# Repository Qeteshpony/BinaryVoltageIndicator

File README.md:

# Binary Voltage Indicator

[Hardware Documentation](https://qeteshpony.github.io/BinaryVoltageIndicator)

A small board that can be attached to a 5V power supply to show if the voltage is above or below 5.0V with a maximum tolerance of about 2% (±0.1V) when 1% resistors are used.

The board can also be directly plugged onto a Raspberry Pi GPIO header to have a quick visual aid about the power supply status. The third pin is an open collector output that pulls down when the voltage is above 5.0V. When plugged onto the GPIO header this gets connected to GPIO14. 

Connections when directly plugged in:

| Board | GPIO Header|
|:------|:-----------|
|  VCC  | 4 (5V)     |
|  GND  | 6 (GND)    |
|  VOK  | 8 (GPIO14) |

When using a cable, VOK can of course be connected to any GPIO Pin or not be used at all. 

The "wings" with the screw holes can be used to mount the board in a case or broken off if they are not needed.

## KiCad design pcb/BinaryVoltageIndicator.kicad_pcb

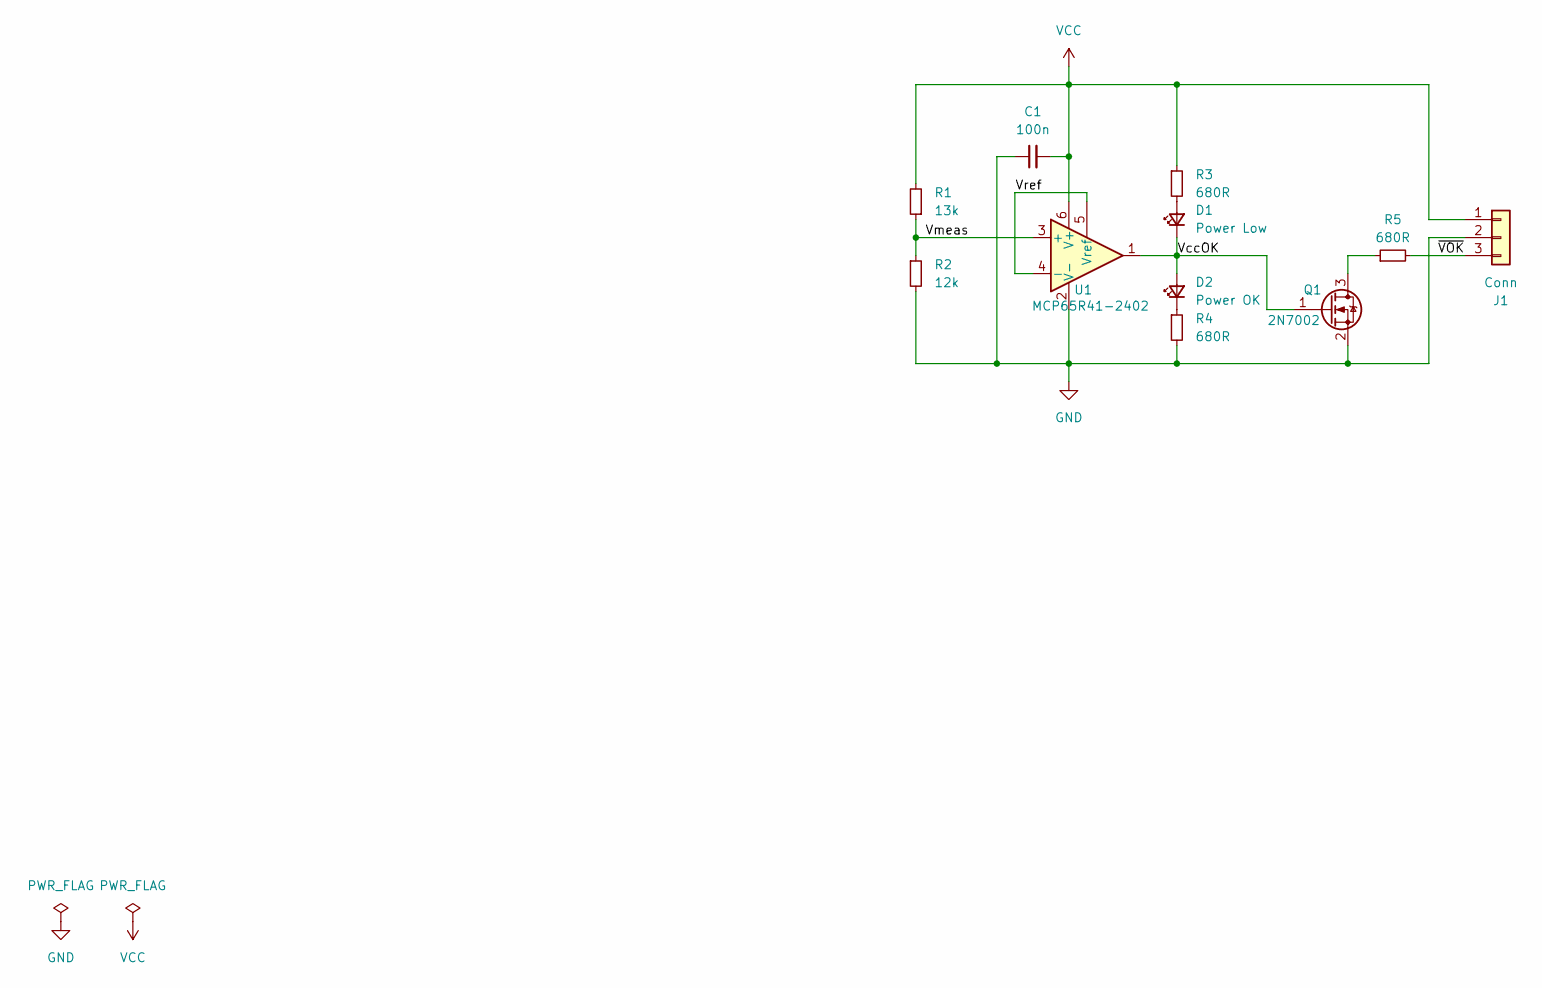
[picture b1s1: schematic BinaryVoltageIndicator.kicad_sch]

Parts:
C1: 100n; C_0402_1005Metric; LCSC C1525
D1: Power Low; LED_0603_1608Metric; LCSC C2286
D2: Power OK; LED_0603_1608Metric; LCSC C2986059
J1: Conn; PinHeader_1x03_P2.54mm_Vertical
Q1: 2N7002; SOT-23; LCSC C8545
R1: 13k; R_0603_1608Metric; LCSC C22797
R2: 12k; R_0603_1608Metric; LCSC C22790
R3, R4, R5: 680R; R_0402_1005Metric; LCSC C25130
U1: MCP65R41-2402; SOT-23-6; LCSC C145386

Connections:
/VccOK: D1.1 (K), D2.2 (A), Q1.1 (G), U1.1
/Vmeas: R1.1, R2.1, U1.3 (+)
/Vref: U1.4 (-), U1.5 (Vref)
/~VOK: J1.3, R5.2
GND: C1.1, J1.2, Q1.2 (S), R2.2, R4.2, U1.2 (V-)
unnamed: D1.2 (A), R3.2
unnamed: D2.1 (K), R4.1
unnamed: Q1.3 (D), R5.1
VCC: C1.2, J1.1, R1.2, R3.1, U1.6 (V+)

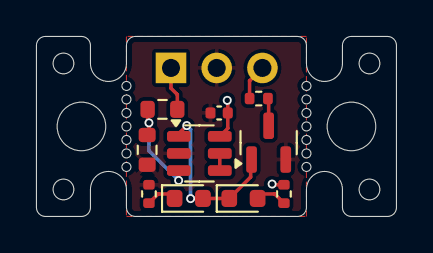
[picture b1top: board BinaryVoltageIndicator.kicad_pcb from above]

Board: 2 copper layers, 20.0 x 10.0 mm, 13 parts (1 on the bottom side), 9 nets.

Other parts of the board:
mouse-bite-2mm-slot, mouse-bite-2mm-slot#2: VAL**; mouse-bite-2x5mm-slot-onesided-v2

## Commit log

2024-07-27 feat: initial release
2024-07-27 chore(main): release 1.0.0
2024-07-27 fix: change measurement resistors to 0603
    the 0402 resistors in JLCPCBs standard library are 5% - too much for this to work properly
2024-07-27 chore(main): release 1.0.1
2024-08-29 ci: remove dependency between jobs
